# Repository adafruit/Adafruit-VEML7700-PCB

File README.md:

## Adafruit VEML7700 Lux Sensor PCB

<a href="http://www.adafruit.com/products/5378"><br/>
Click here to purchase the right-angle STEMMA QT version from the Adafruit shop</a>
<a href="http://www.adafruit.com/products/4162"><br/>
Click here to purchase the original version from the Adafruit shop</a>

PCB files for the Adafruit VEML7700 Lux Sensor. Format is EagleCAD schematic and board layout
* https://www.adafruit.com/product/4162

### Description

Vishay has a lot of light sensors out there, and this is a nice simple lux sensor that's easy to add to any microcontoller. Most light sensors just give you a number for brighter/darker ambient lighting. The VEML7700 makes your life easier by calculating the lux, which is an SI unit for light. You'll get more consistent readings between multiple sensors because you aren't dealing with some unit-less values.

The sensor has 16-bit dynamic range for ambient light detection from 0 lux to about 120 klux with resolution down to 0.0036 lx/ct, with software-adjustable gain and integration times.

Interfacing is easy - this sensor uses plain, universal I2C. We put this sensor on a breakout board with a 3.3V regulator and logic level shifter so you can use it with 3.3V or 5V power/logic microcontrollers. [We have written libraries for Arduino (C/C++)](https://github.com/adafruit/Adafruit_VEML7700) as well as [CircuitPython (Python 3)]https://github.com/adafruit/Adafruit_CircuitPython_VEML7700) so you can use this sensor with just about any kind of device, even a Raspberry Pi!

The PID 5378 version is also one of the very few light/lux sensors we've ever seen that is right angle - that means that it senses light that is coming parallel to the PCB surface not perpendicular.

As with all Adafruit breakouts, we've done the work to make this handy light sensor super easy to use. We've put it on a breakout board with the required support circuitry and connectors to make it easy to work with. Since I2C is supported, we've added SparkFun Qwiic compatible STEMMA QT JST SH connectors that allow you to get going without needing to solder. Just use a STEMMA QT adapter cable, plug it into your favorite microcontroller or Blinka supported SBC and you're ready to rock! QT Cable is not included, but we have a variety in the shop.  

This is Kattni's first PCB design for Adafruit, it's even signed on the back!?

### License

Adafruit invests time and resources providing this open source design, please support Adafruit and open-source hardware by purchasing products from [Adafruit](https://www.adafruit.com)!

Designed by Kattni Rembor for Adafruit Industries.

Creative Commons Attribution/Share-Alike, all text above must be included in any redistribution. See license.txt for additional details.

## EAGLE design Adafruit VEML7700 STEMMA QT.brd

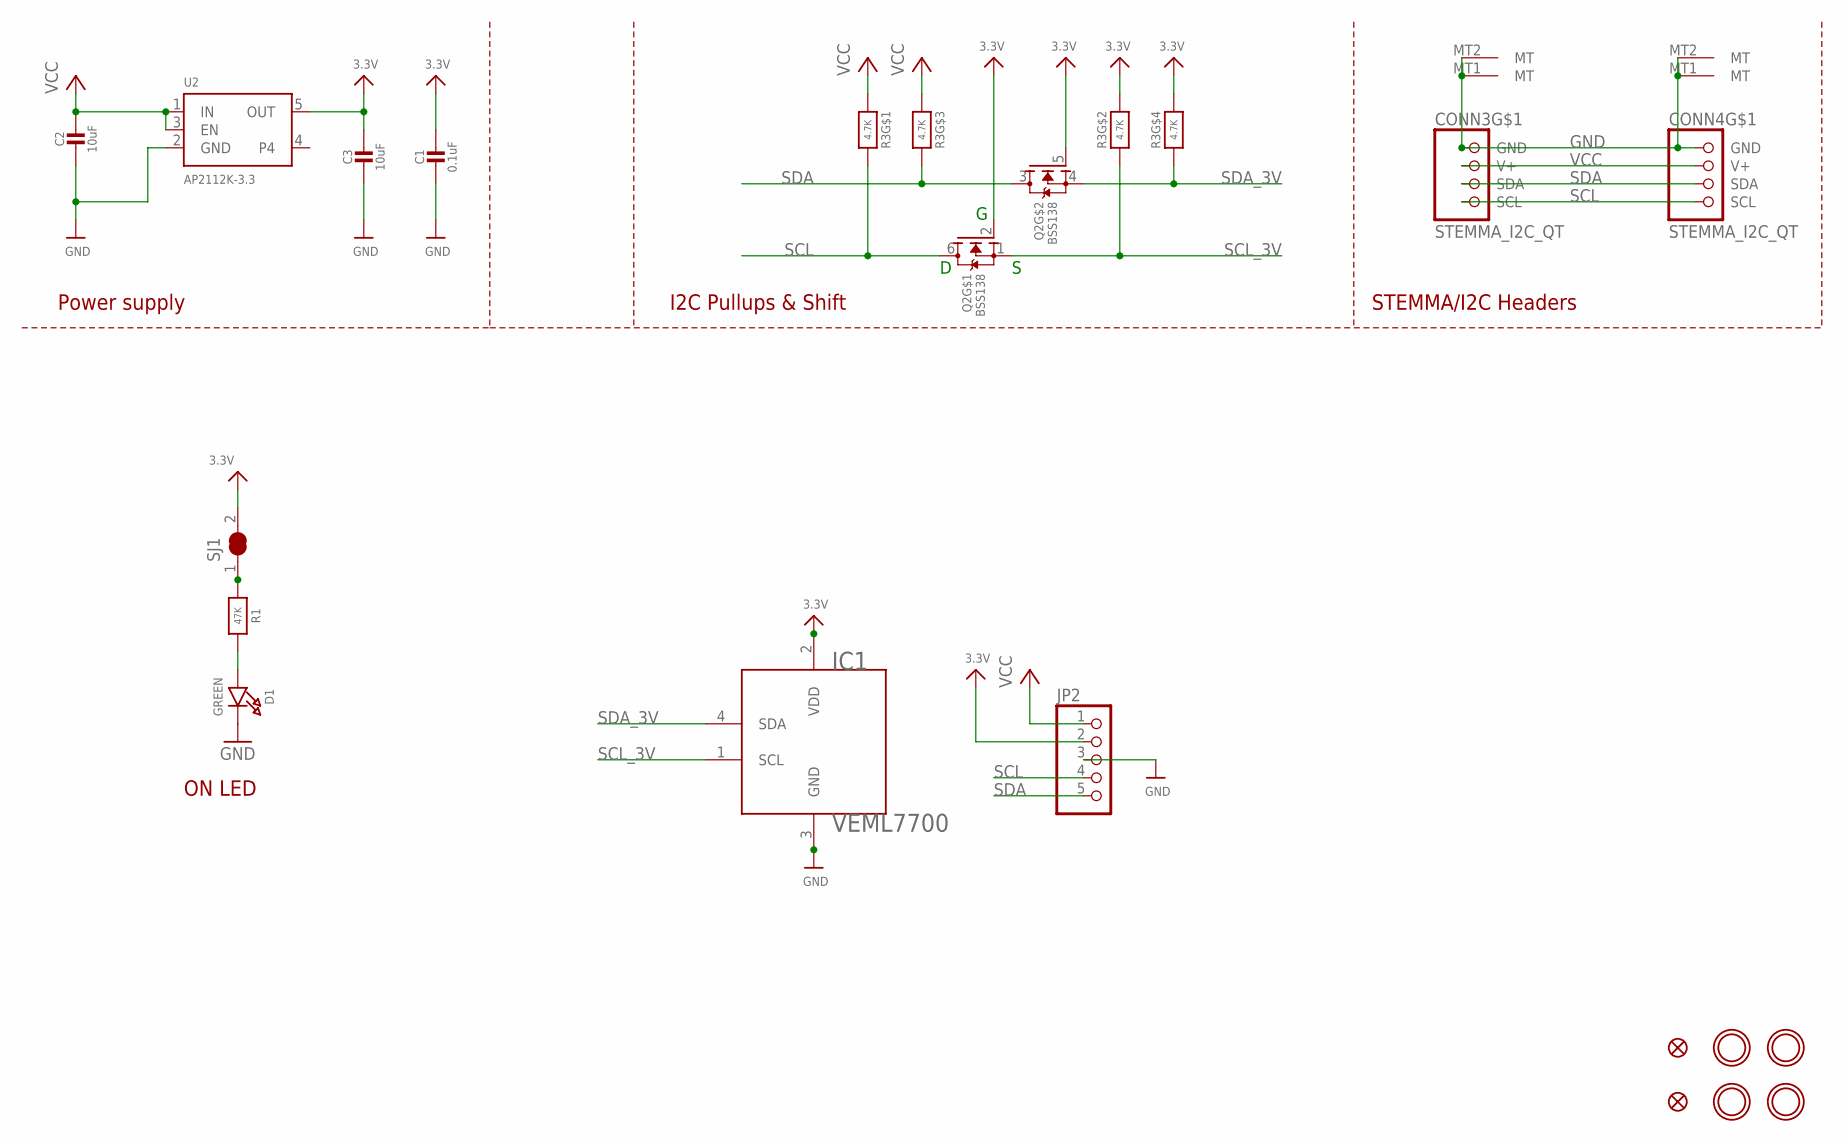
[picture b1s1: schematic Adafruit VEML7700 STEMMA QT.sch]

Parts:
C1: 0.1uF; 0603-NO
C2, C3: 10uF; 0805-NO
CONN3, CONN4: STEMMA_I2C_QT; JST_SH4
D1: GREEN; CHIPLED_0603_NOOUTLINE
FID3, FID4: FIDUCIAL_1MM
IC1: VEML7700
JP2: HEADER-1X5ROUND; 1X05_ROUND
Q2: BSS138; SOT363
R1: 47K; 0603-NO
R3: 4.7K; RESPACK_4X0603
SJ1: SOLDERJUMPER_CLOSED; SOLDERJUMPER_CLOSEDWIRE
U2: AP2112K-3.3; SOT23-5
U$1, U$17, U$19, U$21: MOUNTINGHOLE2.5; MOUNTINGHOLE_2.5_PLATED

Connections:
3.3V: C1.1, C3.1, IC1.2 (VDD), JP2.2, Q2.2 (G), Q2.5 (G), R3.2 (1), R3.4 (1), SJ1.2, U2.5 (OUT)
GND: C1.2, C2.2, C3.2, CONN3.1 (GND), CONN3.MT1 (MT), CONN3.MT2 (MT), CONN4.1 (GND), CONN4.MT1 (MT), CONN4.MT2 (MT), D1.C, IC1.3 (GND), JP2.3, U2.2 (GND)
unnamed: D1.A, R1.2
unnamed: R1.1, SJ1.1
SCL: CONN3.4 (SCL), CONN4.4 (SCL), JP2.4, Q2.6 (D), R3.8 (2)
SCL_3V: IC1.1 (SCL), Q2.1 (S), R3.7 (2)
SDA: CONN3.3 (SDA), CONN4.3 (SDA), JP2.5, Q2.3 (D), R3.6 (2)
SDA_3V: IC1.4 (SDA), Q2.4 (S), R3.5 (2)
VCC: C2.1, CONN3.2 (V+), CONN4.2 (V+), JP2.1, R3.1, R3.3 (1), U2.1 (IN), U2.3 (EN)

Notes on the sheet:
I2C Pullups & Shift
STEMMA/I2C Headers
ON LED
Power supply

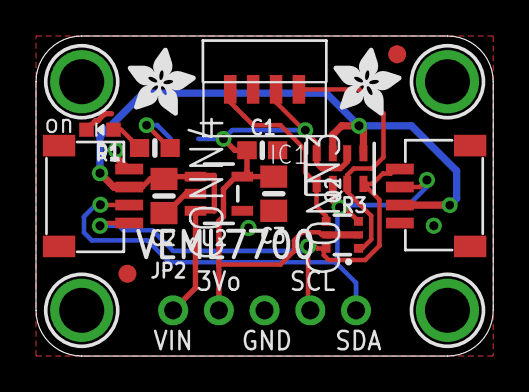
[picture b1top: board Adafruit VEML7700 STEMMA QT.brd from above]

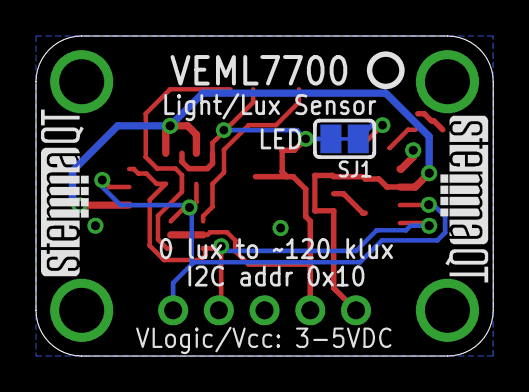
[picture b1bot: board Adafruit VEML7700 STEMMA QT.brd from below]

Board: 2 copper layers, 25.4 x 17.8 mm, 25 parts (5 on the bottom side), 9 nets.

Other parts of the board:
U$2: KATTNI_STOP
U$4, U$22: ADAFRUIT_3.5MM
U$25: PCBFEAT-REV-040
U$30, U$31: STEMMAQT

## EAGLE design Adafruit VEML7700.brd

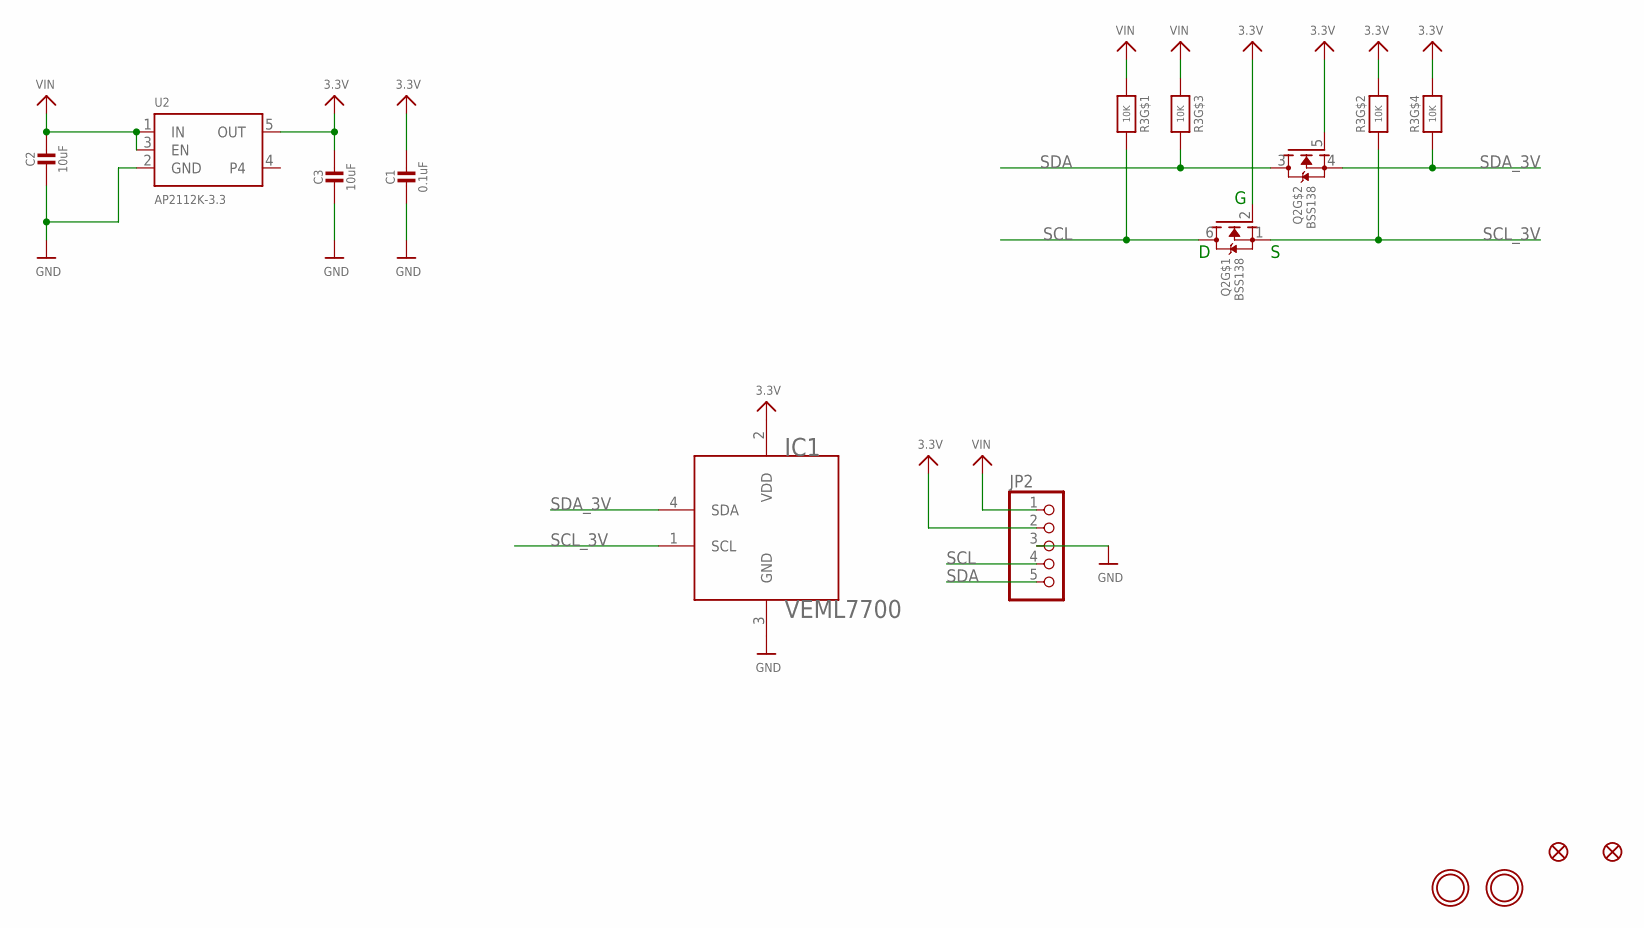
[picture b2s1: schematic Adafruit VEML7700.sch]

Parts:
C1: 0.1uF; 0603-NO
C2, C3: 10uF; 0805-NO
FID1, FID2: FIDUCIAL_1MM
IC1: VEML7700
JP2: HEADER-1X5ROUND; 1X05_ROUND
Q2: BSS138; SOT363
R3: 10K; RESPACK_4X0603
U2: AP2112K-3.3; SOT23-5
U$3, U$4: MOUNTINGHOLE2.5; MOUNTINGHOLE_2.5_PLATED

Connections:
3.3V: C1.1, C3.1, IC1.2 (VDD), JP2.2, Q2.2 (G), Q2.5 (G), R3.2 (1), R3.4 (1), U2.5 (OUT)
GND: C1.2, C2.2, C3.2, IC1.3 (GND), JP2.3, U2.2 (GND)
SCL: JP2.4, Q2.6 (D), R3.8 (2)
SCL_3V: IC1.1 (SCL), Q2.1 (S), R3.7 (2)
SDA: JP2.5, Q2.3 (D), R3.6 (2)
SDA_3V: IC1.4 (SDA), Q2.4 (S), R3.5 (2)
VIN: C2.1, JP2.1, R3.1, R3.3 (1), U2.1 (IN), U2.3 (EN)

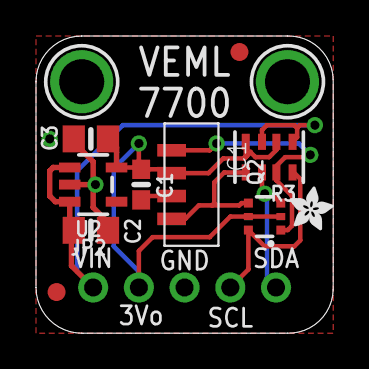
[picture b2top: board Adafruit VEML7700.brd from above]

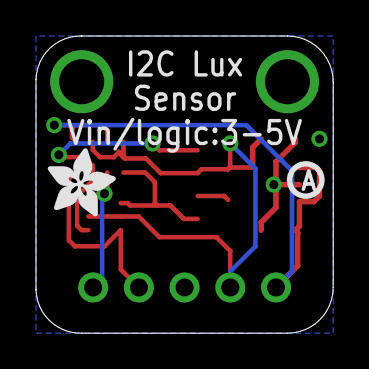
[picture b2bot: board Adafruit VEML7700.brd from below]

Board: 2 copper layers, 16.5 x 16.5 mm, 16 parts (3 on the bottom side), 7 nets.

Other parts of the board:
U$1: ADAFRUIT_3.5MM
U$8: ADAFRUIT_2.5MM
U$12: KATTNI_STOP
U$27: PCBFEAT-REV-040

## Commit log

2019-03-28 Adding brd/sch files
2019-07-17 updated to use cookiecutter for pcb repos
2022-02-11 Add STEMMA QT board files.
2022-02-11 Add asset.

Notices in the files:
parts and their libraries:
microbuilder: This work is placed in the public domain, and may be freely used for commercial and non-commercial work with the following conditions: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
